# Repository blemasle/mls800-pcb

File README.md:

# MLS800 PCBs

The MLS800 is an open-source 1U rack unit MIDI controlled Loop Switcher with 8 audio loops.  

* 8 independent audio loops
* 128 presets
* Active preset is remotly controlled through MIDI `Program Change` messages
* Easy to read through a 4 digits 7 segments display and 9 illuminated switches

This repository contains KiCad files needed to produce the two PCBs.  

</img>&nbsp;
</img>

See the [documentation](https://blemasle.github.io/mls800) for futher info on the project.

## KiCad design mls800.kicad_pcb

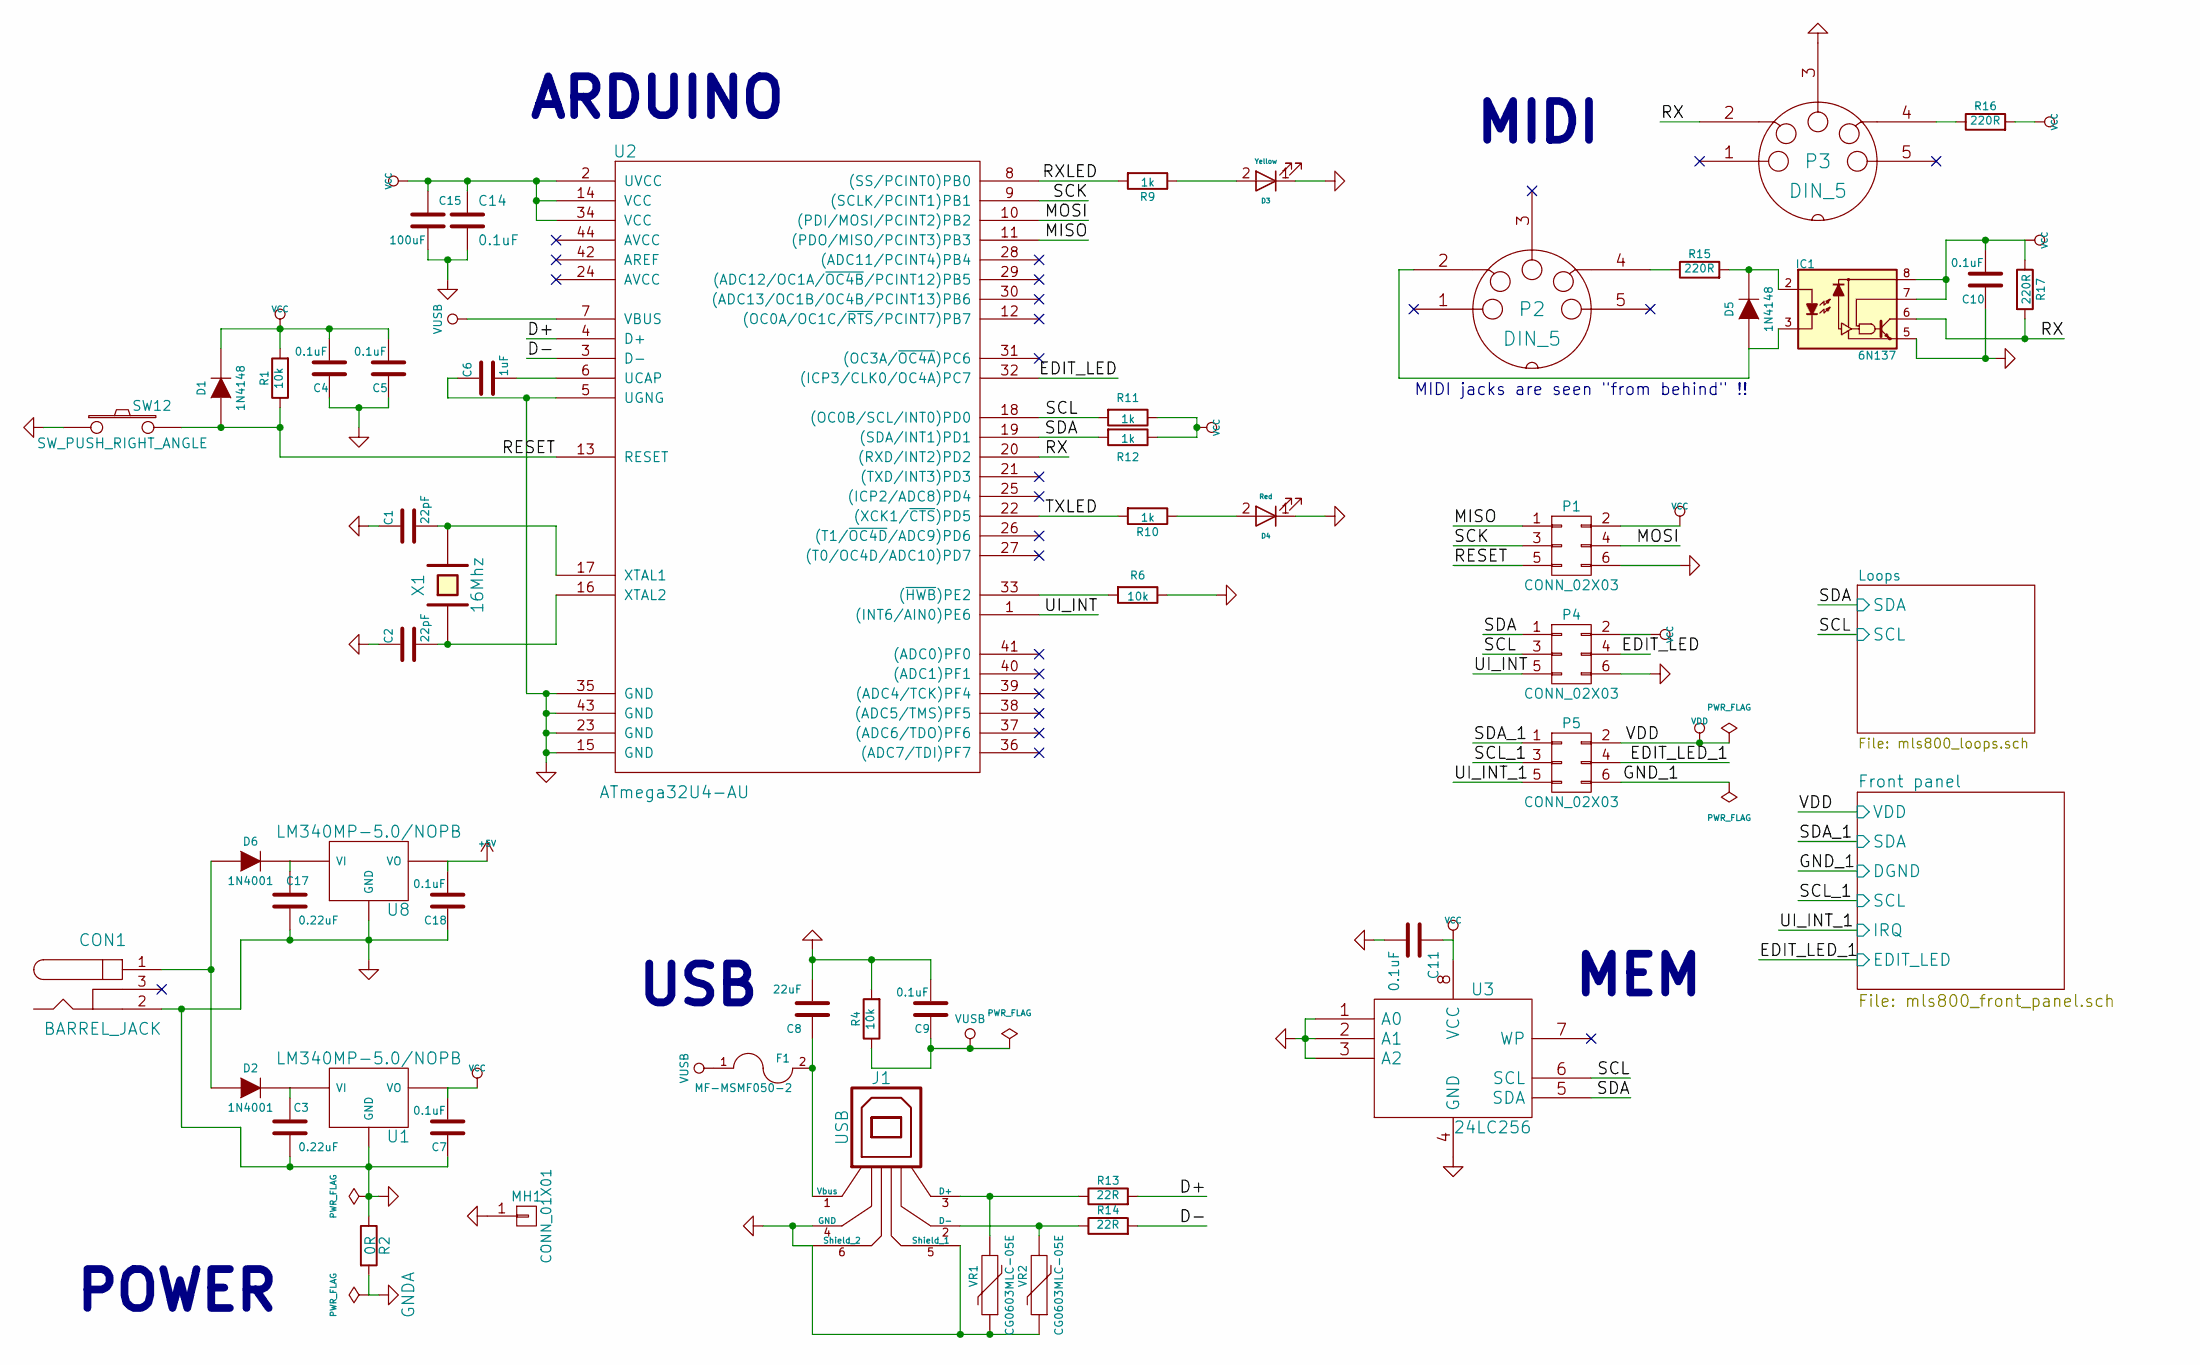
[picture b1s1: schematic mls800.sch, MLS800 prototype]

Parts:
C1, C2: 22pF; C_0805_HandSoldering; Manufacturer part number C0805C220K3GACTU
C3, C17: 0.22uF; C_0805_HandSoldering; Manufacturer part number C0805C224K3RACTU
C4, C5, C7, C9, C10, C11, C14, C18: 0.1uF; C_0805_HandSoldering; Manufacturer part number C0805C104M3RACTU
C6: 1uF; C_0805_HandSoldering; Manufacturer part number C0805C105K3RACTU
C8: 22uF; C_1210_HandSoldering; Manufacturer part number C1210C226K4RACTU
C15: 100uF; c_elec_6.3x7.7; Manufacturer part number EEE-TPC101XAP
CON1: BARREL_JACK; JACK_ALIM; Manufacturer part number RAPC722X
D1, D5: 1N4148; SOD-123_Handsoldering; Manufacturer part number 1N4148W-E3-08
D2, D6: 1N4001; Diode-SMA_Handsoldering; Manufacturer part number S1A-13-F
D3: Yellow; LED-0805; Manufacturer part number APT2012SYCK
D4: Red; LED-0805; Manufacturer part number APT2012EC
F1: MF-MSMF050-2; SMD-1812; Manufacturer part number MF-MSMF050-2
IC1: 6N137; DIP-8_SMD; Manufacturer part number 6N137SM
J1: USB; USB_B; Manufacturer part number 67068-8000
MH1: CONN_01X01; 1pin
P1, P4, P5: CONN_02X03; VASCH3x2; Manufacturer part number 75869-131LF
P2, P3: DIN_5; Manufacturer part number 5212044-1
R1, R4, R6: 10k; R_0805_HandSoldering; Manufacturer part number ERJ-6GEYJ103V
R2: 0R; R_0805_HandSoldering; Manufacturer part number ERJ-6GEY0R00V
R9, R10, R11, R12: 1k; R_0805_HandSoldering; Manufacturer part number ERJ-6GEYJ102V
R13, R14: 22R; R_0805_HandSoldering; Manufacturer part number ERJ-P06J220V
R15, R16, R17: 220R; R_0805_HandSoldering; Manufacturer part number ERJ-6GEYJ221V
SW12: SW_PUSH_RIGHT_ANGLE; Manufacturer part number MJTP1236
U1, U8: LM340MP-5.0/NOPB; SOT-223; Manufacturer part number LM340MP-5.0/NOPB
U2: ATmega32U4-AU; TQFP-44_10x10mm_Pitch0.8mm; Manufacturer part number ATMega32U4-AU
U3: 24LC256; SOIC-8_3.9x4.9mm_Pitch1.27mm; Manufacturer part number 24LC256I/SN
VR1, VR2: CG0603MLC-05E; R_0603_HandSoldering; Manufacturer part number CG0603MLC-05E
X1: 16Mhz; Q_49U3HMS; Manufacturer part number ECS-160-20-5PX-TR

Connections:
+5V: C18.2, U8.3 (VO); also elsewhere on the board
/D+: R13.2, U2.4 (D+)
/D-: R14.2, U2.3 (D-)
/EDIT_LED: P4.4, U2.32 ((ICP3/CLK0/OC4A)PC7)
/EDIT_LED_1: P5.4; also elsewhere on the board
/GND_1: P5.6; also elsewhere on the board
/MISO: P1.1, U2.11 ((PDO/MISO/PCINT3)PB3)
/MOSI: P1.4, U2.10 ((PDI/MOSI/PCINT2)PB2)
/RESET: D1.1 (A), P1.5, R1.1, SW12.2, U2.13 (RESET)
/RX: IC1.6, P3.2, R17.2, U2.20 ((RXD/INT2)PD2)
/RXLED: R9.2, U2.8 ((SS/PCINT0)PB0)
/SCK: P1.3, U2.9 ((SCLK/PCINT1)PB1)
/SCL: P4.3, R12.2, U2.18 ((OC0B/SCL/INT0)PD0), U3.6 (SCL); also elsewhere on the board
/SCL_1: P5.3; also elsewhere on the board
/SDA: P4.1, R11.2, U2.19 ((SDA/INT1)PD1), U3.5 (SDA); also elsewhere on the board
/SDA_1: P5.1; also elsewhere on the board
/TXLED: R10.2, U2.22 ((XCK1/~CTS~)PD5)
/UI_INT: P4.5, U2.1 ((INT6/AIN0)PE6)
/UI_INT_1: P5.5; also elsewhere on the board
GND: C1.1, C2.1, C3.1, C4.1, C5.1, C6.1, C7.1, C8.2, C9.2, C10.1, C11.2, C14.2, C15.2, C17.1, C18.1, CON1.2, D3.1 (K), D4.1 (K), IC1.5, J1.4 (GND), J1.5 (Shield_1), J1.6 (Shield_2), MH1.1, P1.6, P2.6 (GND), P2.7 (GND), P3.3, P3.6 (GND), P3.7 (GND), P4.6, R2.1, R4.2, R6.1, SW12.1, SW12.3 (GND), SW12.4 (GND), U1.2 (GND), U1.4 (GND), U2.5 (UGNG), U2.15 (GND), U2.23 (GND), U2.35 (GND), U2.43 (GND), U3.1 (A0), U3.2 (A1), U3.3 (A2), U3.4 (GND), U8.2 (GND), U8.4 (GND), VR1.1, VR2.1; also elsewhere on the board
GNDA: R2.2; also elsewhere on the board
unnamed: C1.2, U2.17 (XTAL1), X1.2
unnamed: C2.2, U2.16 (XTAL2), X1.1
unnamed: C3.2, D2.2 (K), U1.1 (VI)
unnamed: C6.2, U2.6 (UCAP)
unnamed: C8.1, F1.2, J1.1 (Vbus)
unnamed: C17.2, D6.2 (K), U8.1 (VI)
unnamed: CON1.1, D2.1 (A), D6.1 (A)
unnamed: D3.2 (A), R9.1
unnamed: D4.2 (A), R10.1
unnamed: D5.1 (A), IC1.3, P2.2
unnamed: D5.2 (K), IC1.2, R15.2
unnamed: J1.2 (D-), R14.1, VR2.2
unnamed: J1.3 (D+), R13.1, VR1.2
unnamed: P2.4, R15.1
unnamed: P3.4, R16.1
unnamed: R6.2, U2.33 ((~HWB~)PE2)
VCC: C4.2, C5.2, C7.2, C10.2, C11.1, C14.1, C15.1, D1.2 (K), IC1.7, IC1.8, P1.2, P4.2, R1.2, R11.1, R12.1, R16.2, R17.1, U1.3 (VO), U2.2 (UVCC), U2.14 (VCC), U2.34 (VCC), U3.8 (VCC); also elsewhere on the board
VCOM: C9.1, F1.1, R4.1, U2.7 (VBUS)
VDD: P5.2; also elsewhere on the board

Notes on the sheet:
POWER
USB
ARDUINO
MEM
MIDI
MIDI jacks are seen "from behind" !!

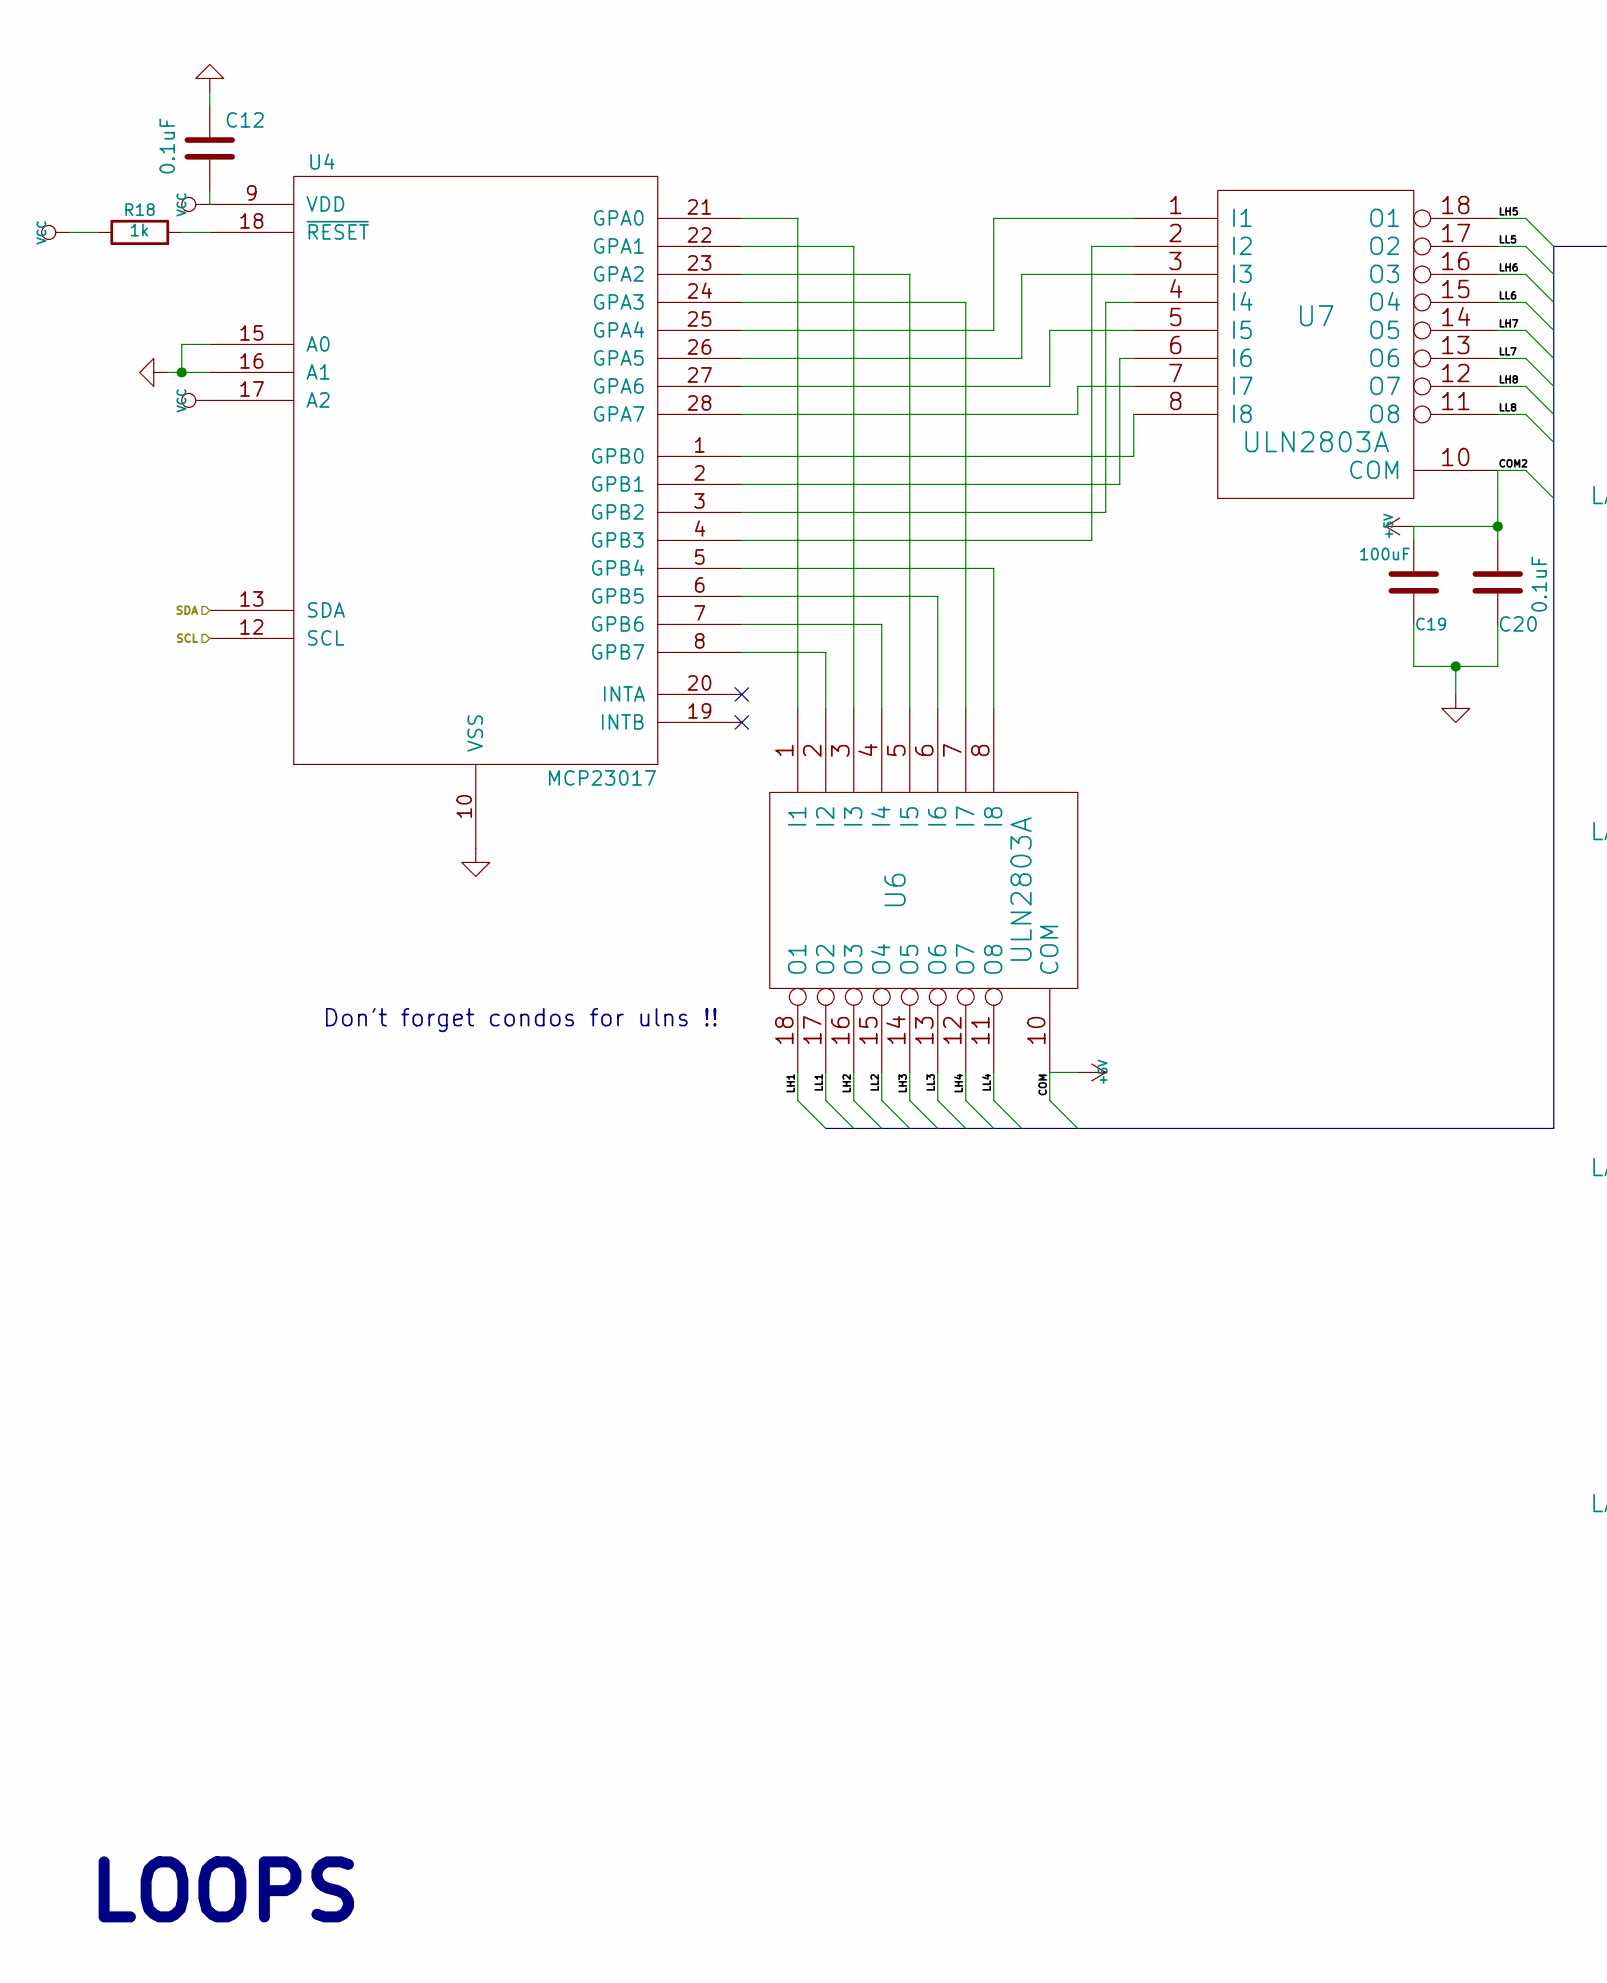
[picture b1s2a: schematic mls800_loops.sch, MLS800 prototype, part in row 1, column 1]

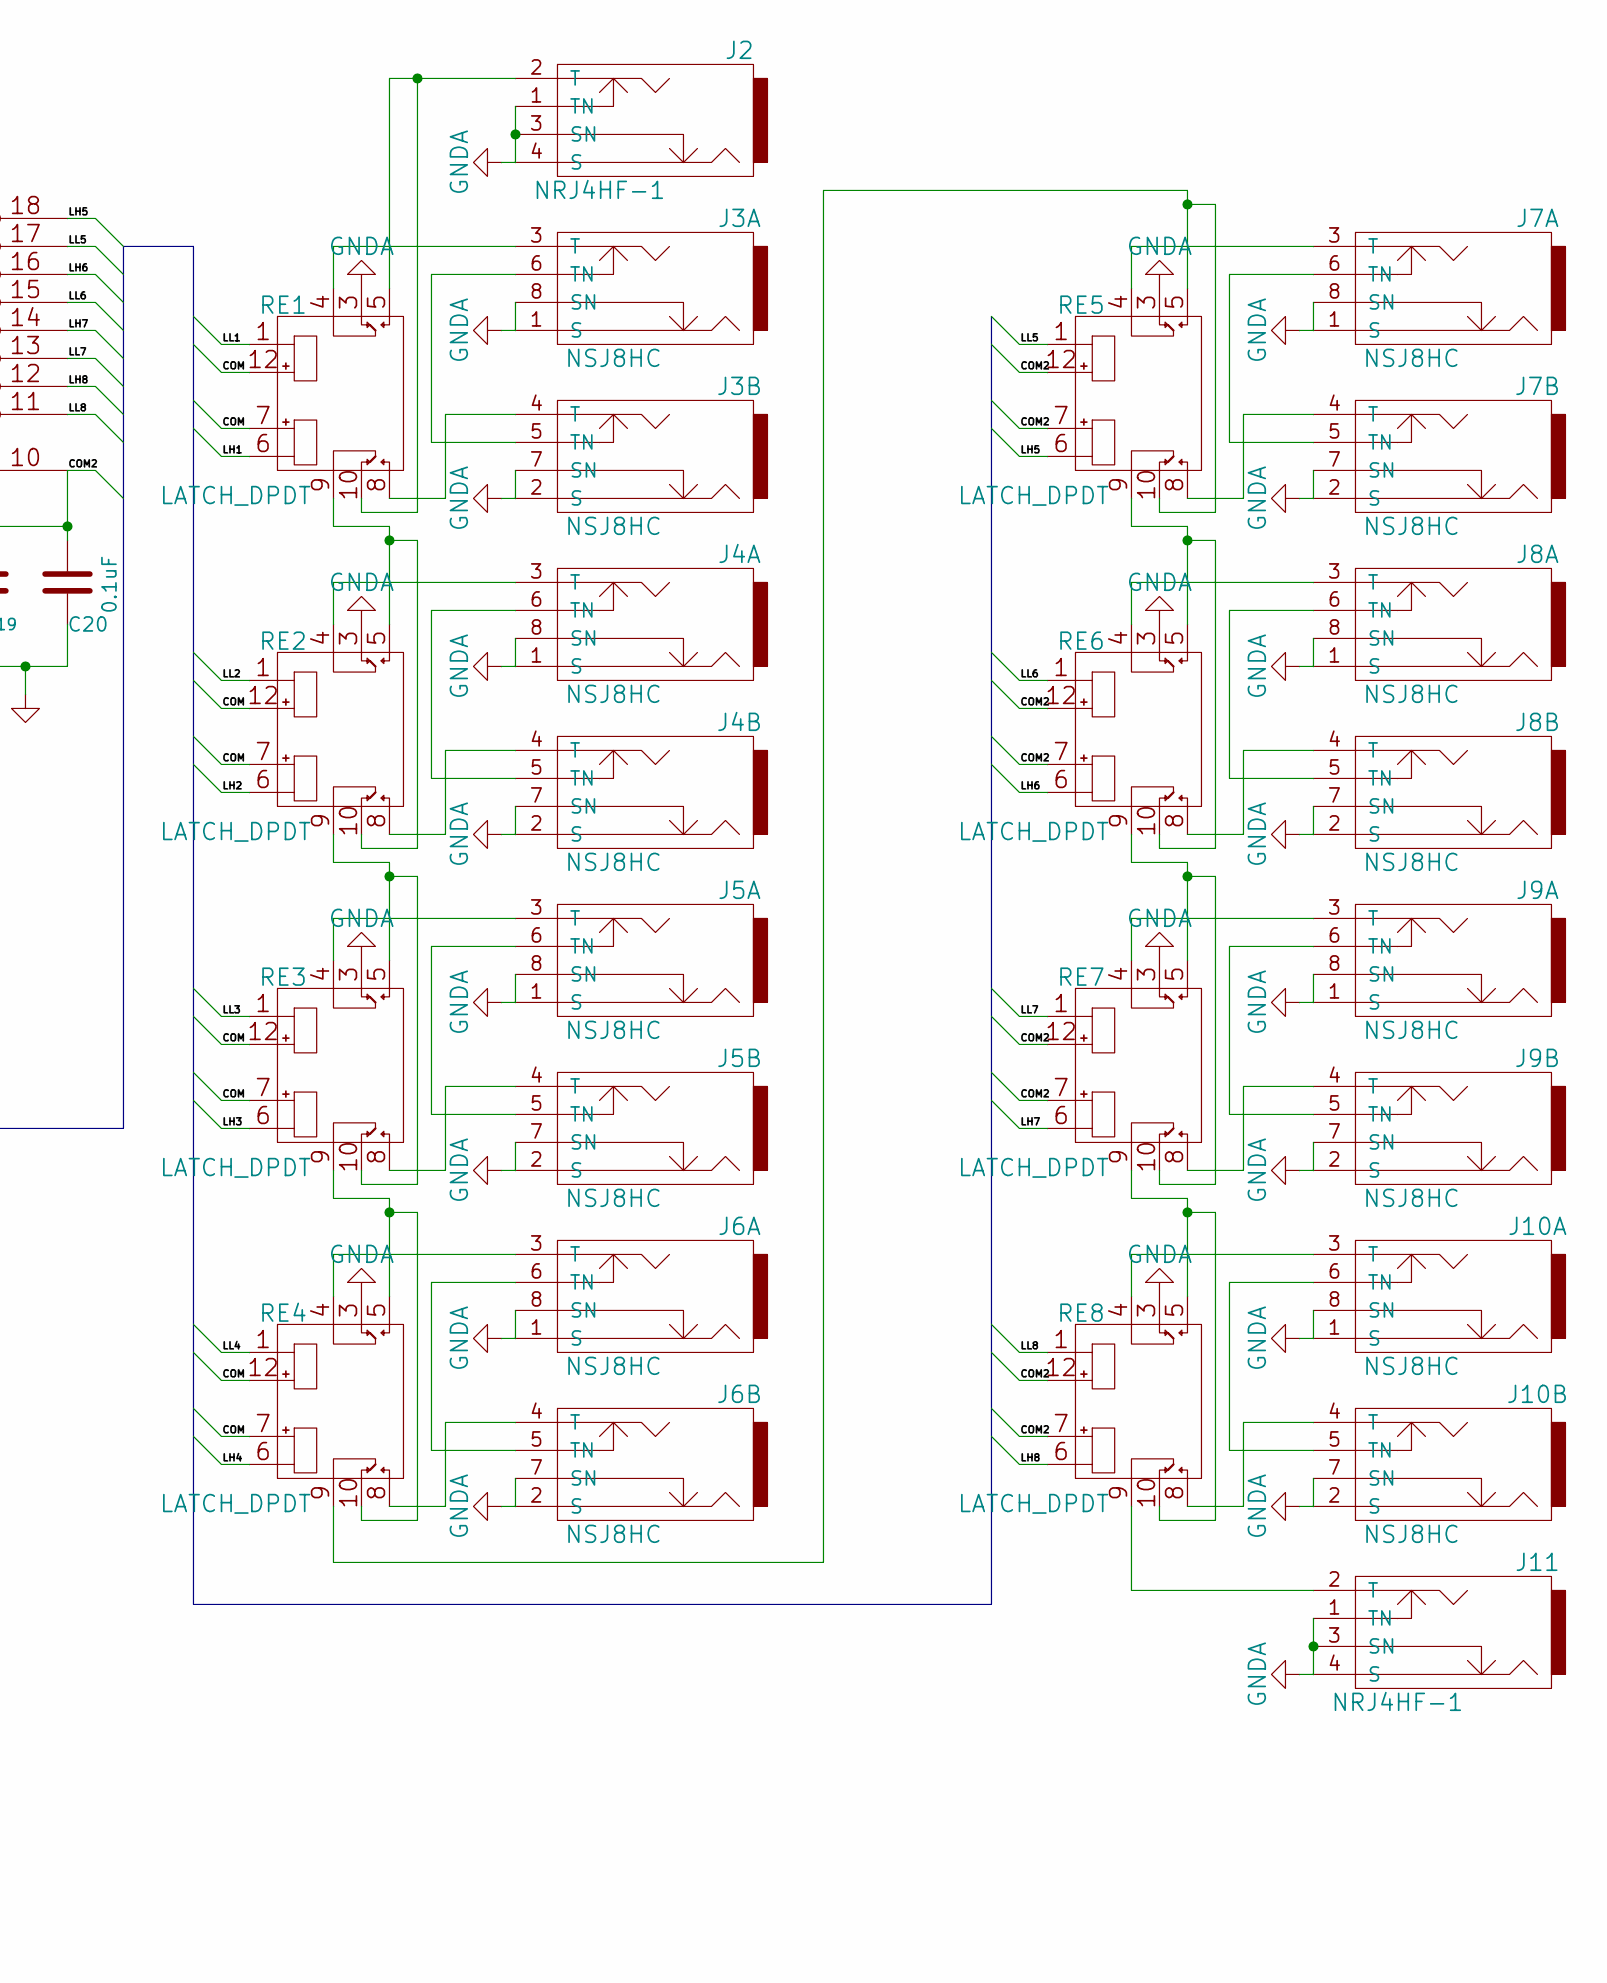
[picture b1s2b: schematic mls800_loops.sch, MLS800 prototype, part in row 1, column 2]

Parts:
C12, C20: 0.1uF; C_0805_HandSoldering; Manufacturer part number C0805C104M3RACTU
C19: 100uF; c_elec_6.3x7.7; Manufacturer part number EEE-TPC101XAP
J2, J11: NRJ4HF-1; Manufacturer part number NRJ4HF-1
J3, J4, J5, J6, J7, J8, J9, J10: NSJ8HC; NSJ8HL; Manufacturer part number NSJ8HC
R18: 1k; R_0805_HandSoldering; Manufacturer part number ERJ-6GEYJ102V
RE1, RE2, RE3, RE4, RE5, RE6, RE7, RE8: LATCH_DPDT; Relay_SMD_DPDT-RT2_bistabil; Manufacturer part number V23079E1201B301
U4: MCP23017; SSOP-28_5.3x10.2mm_Pitch0.65mm; Manufacturer part number MCP23017-E/SS
U6, U7: ULN2803A; SOIC-18_7.5x11.6mm_Pitch1.27mm; Manufacturer part number ULN2803ADW

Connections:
+5V: C19.1, C20.2, RE1.7, RE1.12, RE2.7, RE2.12, RE3.7, RE3.12, RE4.7, RE4.12, RE5.7, RE5.12, RE6.7, RE6.12, RE7.7, RE7.12, RE8.7, RE8.12, U6.10 (COM), U7.10 (COM); also elsewhere on the board
/Loops/LH1: RE1.6, U6.18 (O1)
/Loops/LH2: RE2.6, U6.16 (O3)
/Loops/LH3: RE3.6, U6.14 (O5)
/Loops/LH4: RE4.6, U6.12 (O7)
/Loops/LH5: RE5.6, U7.18 (O1)
/Loops/LH6: RE6.6, U7.16 (O3)
/Loops/LH7: RE7.6, U7.14 (O5)
/Loops/LH8: RE8.6, U7.12 (O7)
/Loops/LL1: RE1.1, U6.17 (O2)
/Loops/LL2: RE2.1, U6.15 (O4)
/Loops/LL3: RE3.1, U6.13 (O6)
/Loops/LL4: RE4.1, U6.11 (O8)
/Loops/LL5: RE5.1, U7.17 (O2)
/Loops/LL6: RE6.1, U7.15 (O4)
/Loops/LL7: RE7.1, U7.13 (O6)
/Loops/LL8: RE8.1, U7.11 (O8)
/SCL: U4.12 (SCL); also elsewhere on the board
/SDA: U4.13 (SDA); also elsewhere on the board
GND: C12.1, C19.2, C20.1, U4.10 (VSS), U4.15 (A0), U4.16 (A1), U6.9 (GND), U7.9 (GND); also elsewhere on the board
GNDA: J2.1 (TN), J2.3 (SN), J2.4 (S), J3.1 (S), J3.2 (S), J3.7 (SN), J3.8 (SN), J3.9 (GNDA), J4.1 (S), J4.2 (S), J4.7 (SN), J4.8 (SN), J4.9 (GNDA), J5.1 (S), J5.2 (S), J5.7 (SN), J5.8 (SN), J5.9 (GNDA), J6.1 (S), J6.2 (S), J6.7 (SN), J6.8 (SN), J6.9 (GNDA), J7.1 (S), J7.2 (S), J7.7 (SN), J7.8 (SN), J7.9 (GNDA), J8.1 (S), J8.2 (S), J8.7 (SN), J8.8 (SN), J8.9 (GNDA), J9.1 (S), J9.2 (S), J9.7 (SN), J9.8 (SN), J9.9 (GNDA), J10.1 (S), J10.2 (S), J10.7 (SN), J10.8 (SN), J10.9 (GNDA), J11.1 (TN), J11.3 (SN), J11.4 (S), RE1.3, RE2.3, RE3.3, RE4.3, RE5.3, RE6.3, RE7.3, RE8.3; also elsewhere on the board
unnamed: J2.2 (T), RE1.5, RE1.10
unnamed: J3.3 (T), RE1.4
unnamed: J3.4 (T), RE1.8
unnamed: J3.5 (TN), J3.6 (TN)
unnamed: J4.3 (T), RE2.4
unnamed: J4.4 (T), RE2.8
unnamed: J4.5 (TN), J4.6 (TN)
unnamed: J5.3 (T), RE3.4
unnamed: J5.4 (T), RE3.8
unnamed: J5.5 (TN), J5.6 (TN)
unnamed: J6.3 (T), RE4.4
unnamed: J6.4 (T), RE4.8
unnamed: J6.5 (TN), J6.6 (TN)
unnamed: J7.3 (T), RE5.4
unnamed: J7.4 (T), RE5.8
unnamed: J7.5 (TN), J7.6 (TN)
unnamed: J8.3 (T), RE6.4
unnamed: J8.4 (T), RE6.8
unnamed: J8.5 (TN), J8.6 (TN)
unnamed: J9.3 (T), RE7.4
unnamed: J9.4 (T), RE7.8
unnamed: J9.5 (TN), J9.6 (TN)
unnamed: J10.3 (T), RE8.4
unnamed: J10.4 (T), RE8.8
unnamed: J10.5 (TN), J10.6 (TN)
unnamed: J11.2 (T), RE8.9
unnamed: R18.2, U4.18 (~RESET)
unnamed: RE1.9, RE2.5, RE2.10
unnamed: RE2.9, RE3.5, RE3.10
unnamed: RE3.9, RE4.5, RE4.10
unnamed: RE4.9, RE5.5, RE5.10
unnamed: RE5.9, RE6.5, RE6.10
unnamed: RE6.9, RE7.5, RE7.10
unnamed: RE7.9, RE8.5, RE8.10
unnamed: U4.1 (GPB0), U7.8 (I8)
unnamed: U4.2 (GPB1), U7.6 (I6)
unnamed: U4.3 (GPB2), U7.4 (I4)
unnamed: U4.4 (GPB3), U7.2 (I2)
unnamed: U4.5 (GPB4), U6.8 (I8)
unnamed: U4.6 (GPB5), U6.6 (I6)
unnamed: U4.7 (GPB6), U6.4 (I4)
unnamed: U4.8 (GPB7), U6.2 (I2)
unnamed: U4.21 (GPA0), U6.1 (I1)
unnamed: U4.22 (GPA1), U6.3 (I3)
unnamed: U4.23 (GPA2), U6.5 (I5)
unnamed: U4.24 (GPA3), U6.7 (I7)
unnamed: U4.25 (GPA4), U7.1 (I1)
unnamed: U4.26 (GPA5), U7.3 (I3)
unnamed: U4.27 (GPA6), U7.5 (I5)
unnamed: U4.28 (GPA7), U7.7 (I7)
VCC: C12.2, R18.1, U4.9 (VDD), U4.17 (A2); also elsewhere on the board

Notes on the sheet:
LOOPS
Don't forget condos for ulns !!

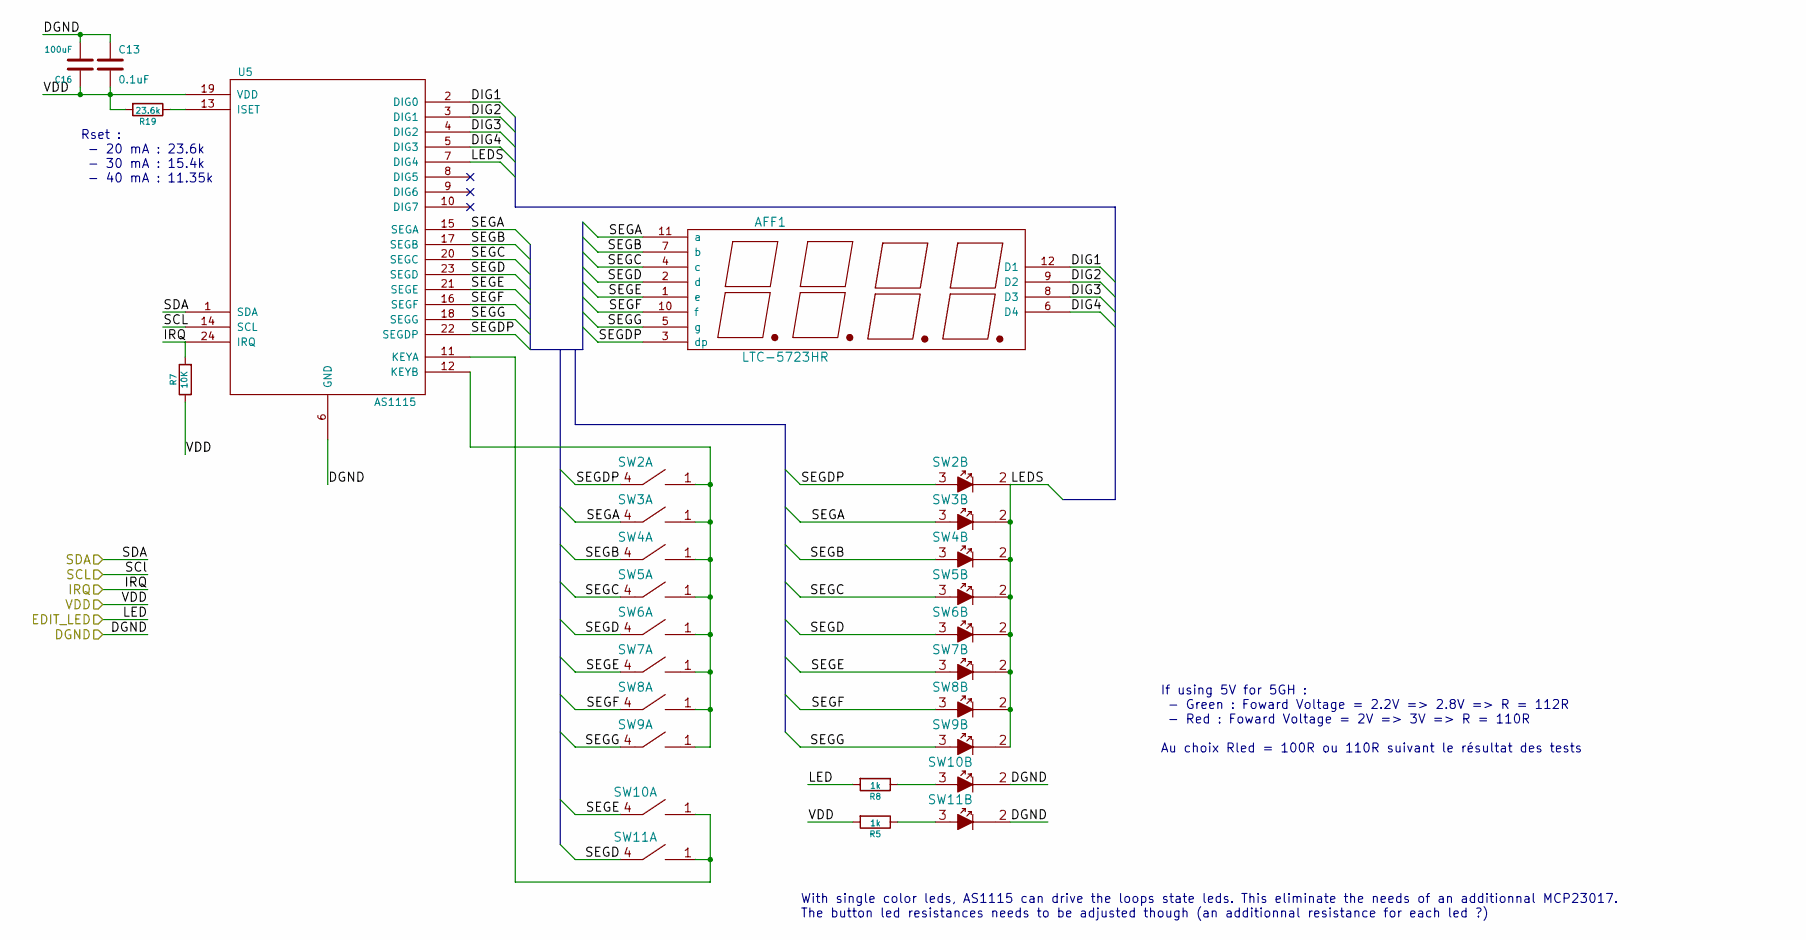
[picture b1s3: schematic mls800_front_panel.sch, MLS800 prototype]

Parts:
AFF1: LTC-5723HR; LTC-5723; Manufacturer part number LTC-5723HR
C13: 0.1uF; C_0805_HandSoldering; Manufacturer part number C0805C104M3RACTU
C16: 100uF; c_elec_6.3x7.7; Manufacturer part number EEE-TPC101XAP
R5, R8: 1k; R_0805_HandSoldering; Manufacturer part number ERJ-6GEYJ102V
R7: 10K; R_0805_HandSoldering; Manufacturer part number ERJ-6GEYJ103V
R19: 23.6k; R_0805_HandSoldering; Manufacturer part number ERJ-6GEYJ243V
SW2, SW3, SW4, SW5, SW6, SW7, SW8, SW9, SW10, SW11: SW_TACT_LED; MEC-5G; Manufacturer part number 5GSH93582
U5: AS1115; SSOP-24_3.9x8.7mm_Pitch0.635mm; Manufacturer part number AS1115-BSST

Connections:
/EDIT_LED_1: R8.2; also elsewhere on the board
/Front panel/DIG1: AFF1.12 (D1), U5.2 (DIG0)
/Front panel/DIG2: AFF1.9 (D2), U5.3 (DIG1)
/Front panel/DIG3: AFF1.8 (D3), U5.4 (DIG2)
/Front panel/DIG4: AFF1.6 (D4), U5.5 (DIG3)
/Front panel/LEDS: SW2.2, SW3.2, SW4.2, SW5.2, SW6.2, SW7.2, SW8.2, SW9.2, U5.7 (DIG4)
/Front panel/SEGA: AFF1.11 (a), SW3.3, SW3.4, U5.15 (SEGA)
/Front panel/SEGB: AFF1.7 (b), SW4.3, SW4.4, U5.17 (SEGB)
/Front panel/SEGC: AFF1.4 (c), SW5.3, SW5.4, U5.20 (SEGC)
/Front panel/SEGD: AFF1.2 (d), SW6.3, SW6.4, SW11.4, U5.23 (SEGD)
/Front panel/SEGDP: AFF1.3 (dp), SW2.3, SW2.4, U5.22 (SEGDP)
/Front panel/SEGE: AFF1.1 (e), SW7.3, SW7.4, SW10.4, U5.21 (SEGE)
/Front panel/SEGF: AFF1.10 (f), SW8.3, SW8.4, U5.16 (SEGF)
/Front panel/SEGG: AFF1.5 (g), SW9.3, SW9.4, U5.18 (SEGG)
/GND_1: C13.1, C16.2, SW10.2, SW11.2, U5.6 (GND); also elsewhere on the board
/SCL_1: U5.14 (SCL); also elsewhere on the board
/SDA_1: U5.1 (SDA); also elsewhere on the board
/UI_INT_1: R7.2, U5.24 (IRQ); also elsewhere on the board
unnamed: R5.1, SW11.3
unnamed: R8.1, SW10.3
unnamed: R19.1, U5.13 (ISET)
unnamed: SW2.1, SW3.1, SW4.1, SW5.1, SW6.1, SW7.1, SW8.1, SW9.1, U5.12 (KEYB)
unnamed: SW10.1, SW11.1, U5.11 (KEYA)
VDD: C13.2, C16.1, R5.2, R7.1, R19.2, U5.19 (VDD); also elsewhere on the board

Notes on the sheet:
Rset : - 20 mA : 23.6k - 30 mA : 15.4k - 40 mA : 11.35k
With single color leds, AS1115 can drive the loops state leds. This eliminate the needs of an additionnal MCP23017. The button led resistances needs to be adjusted though (an additionnal resistance for each led ?)
If using 5V for 5GH : - Green : Foward Voltage = 2.2V => 2.8V => R = 112R - Red : Foward Voltage = 2V => 3V => R = 110R Au choix Rled = 100R ou 110R suivant le résultat des tests

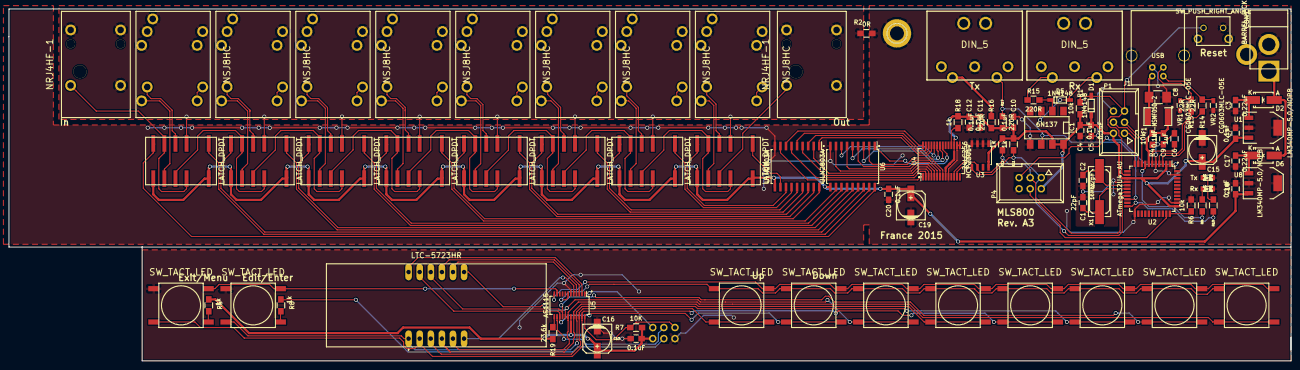
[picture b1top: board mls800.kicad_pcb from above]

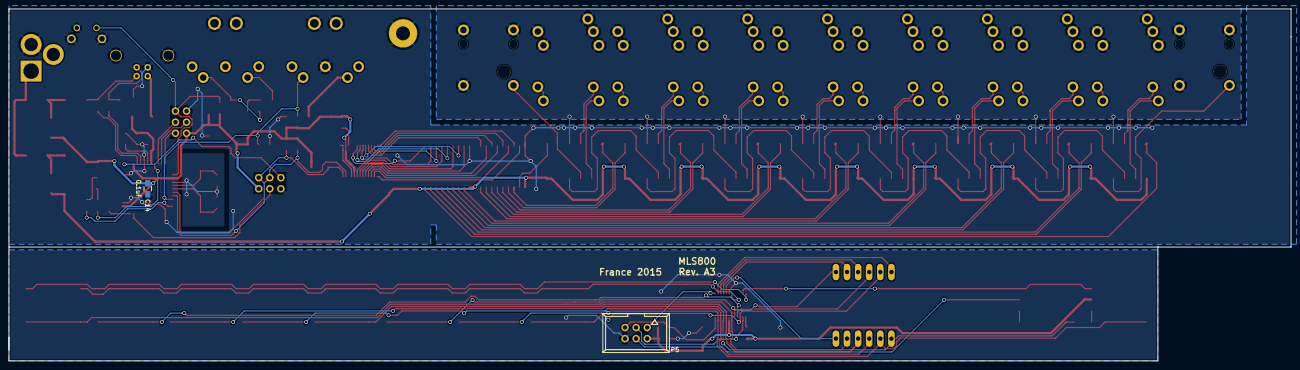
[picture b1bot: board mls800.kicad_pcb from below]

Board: 2 copper layers, 293.4 x 80.5 mm, 95 parts (2 on the bottom side), 124 nets.

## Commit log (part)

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2014-05-20 Move Kicad files to dedicated folder
2014-06-23 MLS800 * Lots of change in diagram/schematic * Added external parts
2014-06-23 MLS800 * Fixed missing non connected symbols
2014-06-24 MLS800 * Fixed some crc errors * Fixed wrong AREF/UCAP schematics * Generated netlist
2014-08-17 MLS800 * Added separated GND : AGND & GND * Revamped the loops schema * Put values on all components * Started to add footprint annotations to some resistors
2014-08-18 MLS800 * Started cmp association
2014-08-27 MLS800 : - assigning footprints
2014-09-29 MLS800 : - added footprints
2014-10-14 MLS800 : created custom librairies
2014-10-15 MLS800 : added LTC-5723HR to custom-display library
    MLS800 : fixed AS1115 pin placement to match main grid
2014-10-15 MLS800 : fixed missing components
2014-10-15 MLS800 : fixed broken layout
    MLS800 : added some comments on schematics rather than using a notepad :)
2014-10-16 MLS800 : disabled switch tact led "interchangeable" units => fixed annotations
    MLS800 : front panel schematic seems to be completed
2014-10-16 MLS800 : disabled switch tact led "interchangeable" units => fixed annotations
    MLS800 : fixed some erc errors in old "misc" sheet
2014-10-16 MLS800 : removed useless power flag
    MLS800 : fixed most errors and warnings
    ATMEGA32U : fixed missing "power input" pins
2014-11-24 MLS800
    * updated layout to match AS1115 diagrams
    * added pull-up resistors
    * removed useless sheets
2014-11-25 MLS800
    * removed unnecessary filter on AVCC & AVCC1
    * removed AREF connection
2014-11-25 MLS800
    * removed note about AREF and AVCCs
2014-11-25 MLS800
    * annotations (again)
    *
2014-11-26 MLS800
    * removed front panel leds resistances
2014-11-28 MLS800
    * footprint associations
2014-12-02 MLS800
    * added two news footprints
    * footprint associations
2014-12-04 MLS800
    * added two news footprints (bistable relay & simple neutrik jack)
    * footprint associations
2014-12-07 MLS800
    * added footprint for double jack
    * footprints assignements
2014-12-07 MLS800
    * fixed simple jack footprint
2014-12-08 MLS800
    * fixed bistable relay pinout
    * fixed lm340 pinout
    * fixed missing footprints from older kicad version
2014-12-12 MLS800
    * started some real pcb
2014-12-17 MLS800
    * routing
    * reversed LL side of the MCP23017 loops control for better layout (needs to be impacted on code side)
2014-12-18 MLS800
    * routing
2014-12-20 MLS800
    * routing : front panel
2014-12-21 MLS800
    * routing : reversed routing of the core pcb
    * footprint placement
2014-12-21 MLS800
    * routing : core pcb & components
2014-12-22 MLS800
    * schematic : added pin header for board connectivity & moved some parts to the front panel layout
    * routing : core pcb & components
2015-01-02 MLS800
    * fixed jacks footprints
2015-01-05 MLS800
    * schematic : changed all 1n4148 to bournes references
    * changed footprints to match bournes ones
    * re routed all the loops part of the pcb
2015-01-05 MLS800
    * adapted filled zones to previous re routing of loops
2015-01-15 MLS800
    * unsplit AGND and DGND
    * retouted relays
    * relayout of gnd zone
2015-01-16 MLS800
    * rerouting
    * changed pad clearance to avoid DRC errors on small footprints
    * set some 3d shapes
2015-01-18 MLS800
    * rerouting
    * copper zones
    * layout optimization
2015-01-19 MLS800
    * rerouting
    * copper zones
    * layout optimization
    * pcb size reduction
    * change u2 to internal kicad library (may induce error in layout, this commit comes just before applying netlist)
2015-01-19 MLS800
    * changed AGND to GND in jack connectors
    * started front panel rerouting
2015-01-20 MLS800
    * splitted schematics for DRC tests
2015-01-21 MLS800
    * solved some VCC supply issues
2015-01-21 MLS800
    * fixed missing relay traces
    * fixed missing vcc traces
2015-01-21 MLS800
    * done most of the routing of the front panel board
2015-01-21 MLS800
    * routing done ? :]
2015-01-22 MLS800
    * gnd zones
    * v-grooving
    * one pcb
2015-01-25 MLS800
    * changed D2 footprint according to availability
2015-01-26 MLS800
    * started rerouting of the main board
2015-01-27 MLS800
    * rerouting of the main board
2015-02-12 MLS800
    * rerouting of some part
    * added filter cap to each digital part
    * added board filter cap
    * set 3d shapes for remaining parts (missing custom parts)
    * added footprint for small pushbutton
2015-02-12 MLS800
    * moved audio jacks to let some spaces for mounting holes
    * rerouted audio jacks
2015-02-16 MLS800
    * mouting holes placement & clearance
    * choosed m3 accroding to http://www.eevblog.com/forum/eda/m3-screw-drill-diameter/
2015-02-18 MLS800
    * mouting holes footprint
    * footprint reference placement
2015-02-18 MLS800
    * copper zone clearance
    * round drilling holes
    *
2015-02-22 MLS800
    * fixed MIDI capacitor being wired to RX rather than GND
2015-02-24 MLS800
    * added ULN2803A
    * relays schematics using 2 of the previous chip
    * added an analog ground for jacks
2015-02-24 Added flyback diodes
2015-02-25 Mixed up pins to made routing easier (needs to be reported on dev side though)
    Started re-routing relays again
2015-02-27 Changed jack pin to GNDA
2015-03-01 Re routed ULN/relays to provide better PCB routing
2015-03-01 Re routed ULN/relays to provide better PCB routing : MCP to ULNS routing
2015-03-01 Relay & Relay drivers alternate routing, saving a lot of space and vias
2015-03-01 Added secondary 5V rails for ULN & relays on schematics & PCB
    Added power supply ripple protection capacitors for ULN
2015-03-01 Resize PCB
    Changed PCB form to stay into "2 panelized" form
2015-03-01 Minor adjustements
2015-03-03 Started final iterations : RC ?
2015-03-04 Minor PCB adjustements
    Fixed R7 tied to ground instead of VCC (needs to be reported on PCB)
2015-03-04 Fixed R7 tied to ground instead of VCC on the PCB
    All relays grounds are now tied to GNDA
2015-03-04 Fixed inverted relays wiring (COM is VDD, not GND)
    Regenerated netlist
2015-03-05 Fixed gnd planes
2015-03-06 Started components fields assignments
2015-03-07 Components fields assignments
    Rerouted relays (set/reset was wired the same way, to reset would have no effect)
    Set and reset port have been exchanged to facilitate routing (to be reported on firmware)
    Edited relay component
2015-03-08 PCB RC2
2015-03-08 Components fields assignments
    Silkscreen dots marker
2015-03-08 Minor changes : RC3
2015-03-09 Ordered PCB (with one major mistake : the two 22R are two small to dissipate 3W !!)
    BOM filling
2015-03-09 Changed reset caps to match other caps values (uF instead of nF)
2015-03-10 Affected most component parts number
2015-03-10 Done components parts number
2015-03-11 Generated BOM csv
2015-03-11 Replace all condos with Kemet ones
    NO solution has been found for the wrong footprint about 100uF condos
2015-03-11 Regenerated BOM
    BOM match the ordered PCBs, with all the mistakes :/
    Tweaked csv BOM so it can be imported into Mouser
    Removed SDS-50J from the BOM as it won't match the footprint
    Added cable stripper parts to the csv BOM
2015-03-24 Fixed SEG_F cannot be used by a switch as AS1115 is in self addressing mode
    Fixed main switches order (DP was last instead of first)
2015-03-24 Fixed silkscreen for up/down buttons
2015-03-24 Fixed C8 begin a tantalum capacitor, replaced with a Kemet 0805 10% ceramic capacitor
2015-03-24 Fixed DIN_5 footprint pins not being aligned with schema part
2015-03-25 Added SOD-123 footprints (to be checked !!)
2015-03-25 Replaced 1n4148 diodes with standard SOD-123 packages from vishay
2015-03-25 Fixed DIN_5 footprint to something more generic (at least most commonly found)
    Created a new DIN_5 component with pin 6 & 7 tied to ground
2015-03-26 Fixed relays schematics by inverting pin 4,3 & 10,9
2015-03-26 Fixed 2x3 pin header footprint
2015-03-26 Regenerated netlist after fixes for PCB REV A2
2015-03-26 Imported new netlist
    Deleted wrong tracks
    Re arrange basic footprints
2015-03-26 Started PCB Rev. A2 layout
2015-03-27 Added vertical push button component & footprint Updated pcb with that last footprint
2015-03-27 usb port power and data routing
2015-03-27 move some parts around usb routing
2015-03-27 Routing of front panel connector
2015-03-27 Optimized routing for copper plane
2015-03-27 Motherboard copper planes were off by a few centimeters Routing of data traces (sda, scl)
2015-03-27 Done routing motherboard logic units
2015-03-27 Found an acceptable routing pattern Started audio jacks routing.
2015-03-27 Routing of audio jacks
2015-03-30 Jacks routing
2015-03-30 Optimized via positions
2015-03-30 Fixed buttons switches nets Regenerated netlist
2015-03-30 Fixed front panel capacitor footprint
2015-03-30 Minor pcb adjustements
2015-03-30 Fixed wrong label name for SEGG button
2015-03-30 Front panel alpha routing
2015-03-30 Front panel routing Copper planes optimizations
2015-03-30 Last commit before leaving train
2015-03-31 Optimized relays nets to allow copper planes to be filled
2015-03-31 Repositionned all elements on a 1.27mm grid
2015-03-31 Front panel routing
2015-04-05 Front panel routing & warnings
2015-04-05 Front panel routing
    Fixed motherboard copper plane on the right side of relays
2015-04-05 Added keepout areas around pin headers
2015-04-05 Fixed front panel ground plane between butons
2015-04-06 Fixed DIN5 footprint pin order
    Fixed SOD-123_Handsoldering footprint
    Placed all components silkscreen
2015-04-06 Fixed front panel PCB outline
    Moved all button silkscreen to the north
2015-04-06 Moved reset button silkscreen closer to the button itself
2015-04-06 Fixed MIDI connectors gap to allow use of another part number if needed
2015-04-06 Fixed sw11 & sw10 ref position
2015-04-06 Fixed MIDI Rx power supply trace width
2015-04-06 Fixed COM being marked as negative on relays
2015-04-06 Added the screw inside the relays nets
2015-04-06 Fixed some silkscreen positions
2015-04-06 Made the MIDI data pin smaller to have a better fit
2015-04-06 PCB cleanup
2015-04-07 Moved SOD-123_Handsoldering to right library
    Updated diodes footprint on PCB
2015-04-07 Regenerated copper planes
2015-04-07 Fixed some 3dshapes
2015-04-08 Changed USB cap to a 1210
    Regenerated netlist
2015-04-08 Imported netlist
    Rearranged USB data & power supply lines
    Added keepout area for Crystal/Atmel VCC & GND net isolation
2015-04-09 Copper planes optimizations
    Ground return paths optimizations
2015-04-09 Cleanup for a3 revision
2015-04-09 Cleanup for pcb rev a3
2015-04-09 Components positioning
2015-04-09 Routing
2015-04-09 PCB routing
2015-04-09 Routing Copper planes Local copper plane for crystal
2015-04-09 Inverted capacitors and crystal position Shifted crystal local ground plane to the left
2015-04-09 Routing Silkscreen placement Moved crystal and caps to the south because of the P1 connector
2015-04-09 Silkcreen positioning for P1 & P4 connectors
2015-04-09 Changed usb capacitor to 1210 (previous change wasn't saved properly)
2015-06-22 Fixed reversed MIDI jacks footprint
2015-07-18 Fixed 6N137 Venabled disconnected
2015-07-18 Fixed jack pins inversions
2015-07-19 Fixed jack pins inversions
    Changed front panel silkscreen text & position
2015-07-19 Change SOD-123 footprint to include cathode annotation once printed
    Added a point marker to ATmega to include pin 1 annotation once printed
2015-07-19 Moved D5 text into view
2015-07-19 Rearranged Tx & Rx leds
2015-07-19 Fixed deleted nest after merge
2015-07-19 Change MJTP1236C to MJTP1236
    Revamped jack wires
2019-01-17 Updated git ignore with more bak/autosave/whatever from KiCad
2019-01-18 Updated schematics to remove warnings & rescue from newest KiCad versions
2019-01-18 Made all necessary changes for the sch to pcb workflow to work again with newest KiCad versions
2019-01-18 Added LICENSE.md and README.md
2019-01-18 Manually added the switches caps to the BOM
2019-01-19 Updated README.md images

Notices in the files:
README.md:
License: GPL License
